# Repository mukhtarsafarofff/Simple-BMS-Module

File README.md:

(ENG) To control the process of charging and discharging of Lithium ion or LiPo batteries, they will stop working or worse. The battery cells can swell and even explode from overcharging, and a deep discharge can make the battery fail.  That’s why these batteries should go together with a battery management system unit or BMS. This will control the voltage and current from the battery and keep them safe. The nominal voltage of a LIPO battery is 3.8 volts and 4.2V when fully charged. As soon as the battery cell will reach this value, the charging process should stop and that’s what this circuit should do. When we have only one cell, we only care about the maximum voltage and the current limit to protect the battery. But when we have a battery pack of more than 1 cell, so 2S, 3S and so on, we also need to balance the value of each individual cell.  At the base of the transistor, we have a ZENNER reference diode (TL431) which will get open at a certain voltage value and by that connects ground to the transistors base and when the transistor is active, we bypass the battery and waste the power on the diodes instead. This ZENNER diode is the TL431 and it has a reference pin, so by adjusting the potentiometer we can set this reference to be at 4.2V, that’s how we select when the charging process will stop. To test the circuit , I  use a battery which is discharged and below 4.2V (it was 3.8V). When I connect it to the charger, the LED is turned off. I have a current flow of around 450 mA and the battery is getting charged up. After some time, when we get above4.16V the LED will turn ON so the charging process is complete. Current is now flowing through the diodes and transistor and we skip the battery, so the cell is protected for over voltage. 

müssen sie richtig überwacht werden, sonst funktionieren sie nicht oder es kann noch schlimmer kommen.  Die Batteriezellen können bei Überladung anschwellen und sogar explodieren, und eine Tiefentladung kann die Batterie unbrauchbar machen. Deshalb sollten diese Batterien immer zusammen mit einer Batterie-Management-System-Einheit (BMS) verwendet werden.  Diese steuert die Spannung und den Strom der Batterie und hält sie sicher. Die Nennspannung einer LiPo-Batterie beträgt 3,8 Volt und 4,2 Volt, wenn sie vollständig geladen ist. Sobald die Batteriezelle diesen Wert erreicht, sollte der Ladevorgang gestoppt werden, und genau das soll diese Schaltung tun. Wenn wir nur eine Zelle haben, kümmern wir uns nur um die maximale Spannung und den Stromgrenzwert, um die Batterie zu schützen. Aber wenn wir ein Batteriepack mit mehr als einer Zelle haben, also 2S, 3S und so weiter, müssen wir auch den Wert jeder einzelnen Zelle ausbalancieren. An der Basis des Transistors haben wir eine Z-Dioden-Referenz (TL431), die bei einem bestimmten Spannungswert öffnet und damit die Basis des Transistors mit Masse verbindet. Wenn der Transistor aktiv ist, umgehen wir die Batterie und verbrauchen die Energie stattdessen an den Dioden. Diese Z-Diode ist die TL431 und sie hat einen Referenzpin. Durch Einstellen des Potentiometers können wir diese Referenz auf 4,2 Volt einstellen, wodurch wir festlegen, wann der Ladevorgang gestoppt wird. Um die Schaltung zu testen, benutze ich eine Batterie, die entladen ist und unter 4,2 Volt liegt (sie hatte 3,8 Volt). Wenn ich sie an das Ladegerät anschließe, ist die LED ausgeschaltet. Ich habe einen Stromfluss von etwa 450 mA und die Batterie wird aufgeladen.  Nach einiger Zeit, wenn wir über 4,16 Volt erreichen, wird die LED eingeschaltet, sodass der Ladevorgang abgeschlossen ist. Der Strom fließt jetzt durch die Dioden und den Transistor und wir umgehen die Batterie, sodass die Zelle vor Überspannung geschützt ist.

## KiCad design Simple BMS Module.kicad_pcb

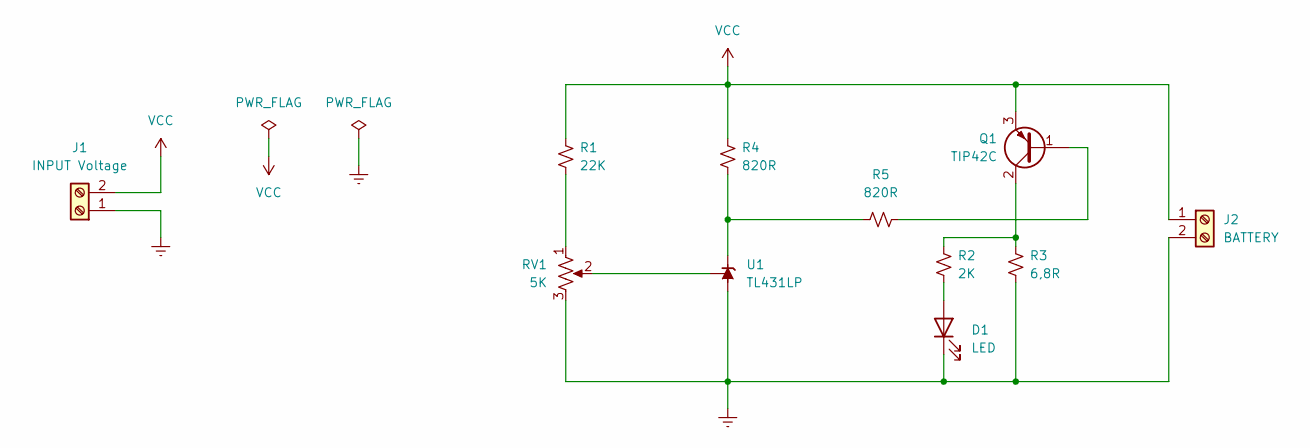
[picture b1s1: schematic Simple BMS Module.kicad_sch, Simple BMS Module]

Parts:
D1: LED; LED_D5.0mm
J1: INPUT Voltage; TerminalBlock_bornier-2_P5.08mm
J2: BATTERY; TerminalBlock_bornier-2_P5.08mm
Q1: TIP42C; TO-220-3_Vertical
R1: 22K; R_Axial_DIN0207_L6.3mm_D2.5mm_P15.24mm_Horizontal
R2: 2K; R_Axial_DIN0207_L6.3mm_D2.5mm_P15.24mm_Horizontal
R3: 6,8R; R_Axial_Power_L25.0mm_W9.0mm_P27.94mm
R4, R5: 820R; R_Axial_DIN0207_L6.3mm_D2.5mm_P15.24mm_Horizontal
RV1: 5K; Potentiometer_Vishay_148-149_Single_Horizontal
U1: TL431LP; TO-92_Inline

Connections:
Earth: D1.1 (K), J1.1, J2.2, R3.2, RV1.3, U1.2 (A)
unnamed: D1.2 (A), R2.2
unnamed: Q1.1 (B), R5.2
unnamed: Q1.2 (C), R2.1, R3.1
unnamed: R1.2, RV1.1
unnamed: R4.2, R5.1, U1.3 (K)
unnamed: RV1.2, U1.1 (REF)
VCC: J1.2, J2.1, Q1.3 (E), R1.1, R4.1

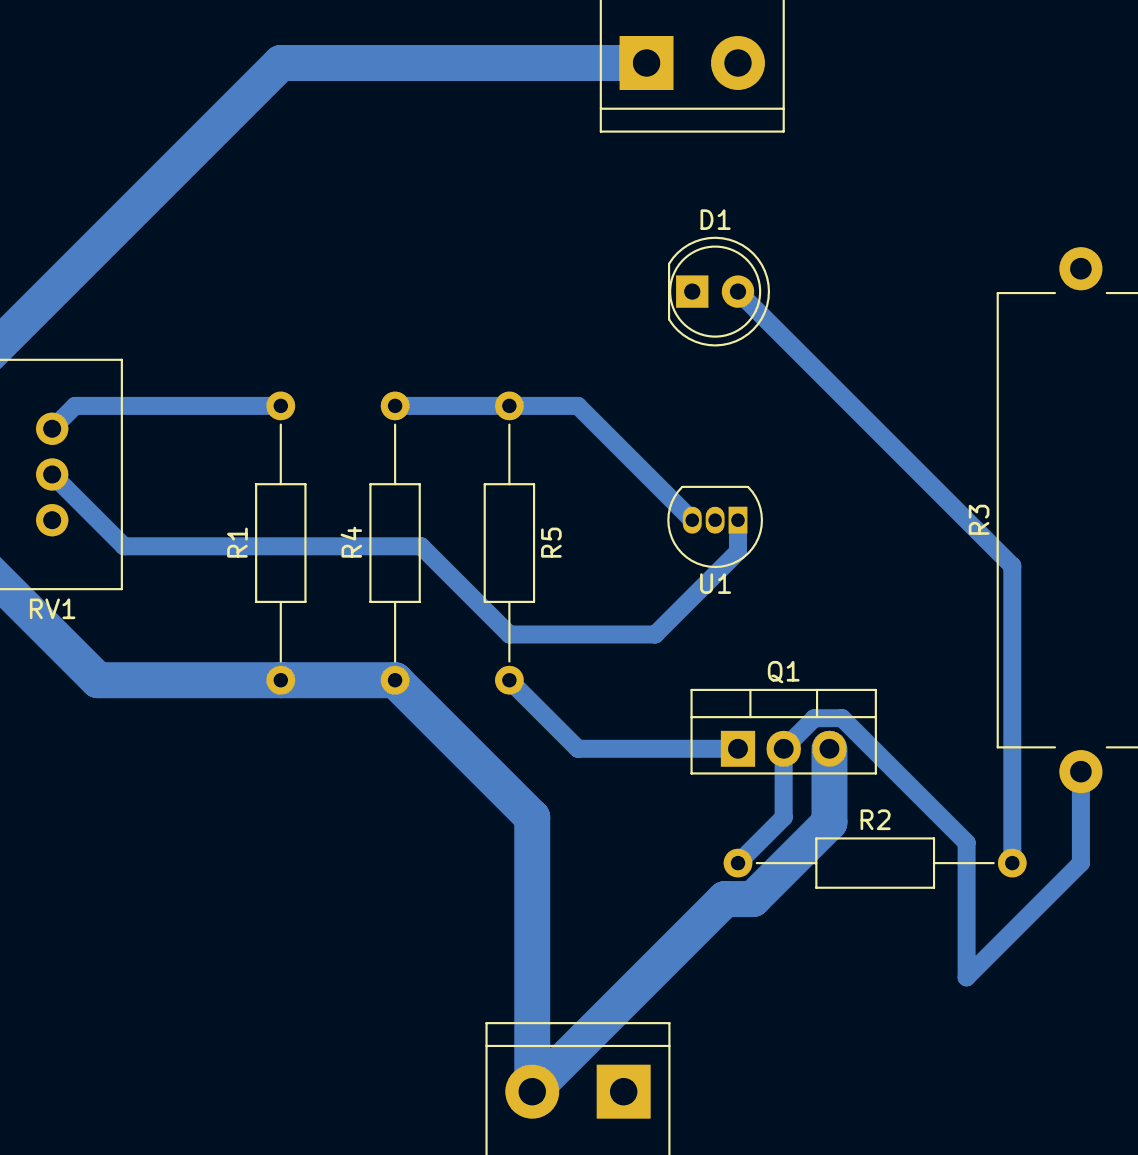
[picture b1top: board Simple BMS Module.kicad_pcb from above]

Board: 2 copper layers, 11 parts (0 on the bottom side), 8 nets.

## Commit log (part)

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2024-03-20 Simple BMS Module is accomplished
2024-03-20 Simple BMS module is renewed
